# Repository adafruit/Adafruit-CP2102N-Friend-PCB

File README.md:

## Adafruit CP2102N Friend - USB to Serial Converter PCB

<a href="http://www.adafruit.com/products/5335"><br/>
Click here to purchase one from the Adafruit shop</a>

PCB files for the Adafruit CP2102N Friend - USB to Serial Converter. 

Format is EagleCAD schematic and board layout
* https://www.adafruit.com/product/5335

### Description

Long gone are the days of parallel ports and serial ports. Now the USB port reigns supreme! But USB is hard, and you just want to transfer your every-day serial data from a microcontroller to computer. What now? Enter the Adafruit CP2102N Friend!

The CP2102N is very similar to the CP2104. Despite having a name with a lower number, its actually considered the successor/next generation to the CP2104. Compared to the CP2104, the CP2102N can:

* Transfer data at a faster rate: CP2104 is 2Mbps max, the CP2102N is 3Mbps max
Reprogram the internal settings: CP2104 has a one-time-programmable memory and the CP2102N has reprogrammable settings memory. 99% of people don't use this capability but it is there if you need it.
* The CP2102N improves over the CP2012 (no N) by having the same RS-485 and GPIO support that the CP2104 has
* More details in the SiLabs CP2104 to CP2102N migration guide.
* We've also updated this breakout from our CP2104 Friend so that it has USB C instead of Micro B. It is otherwise 'drop in compatible' and anywhere you would use the CP2104 for uploading firmware to microcontrollers, it'll work exactly the same.

This is a high-quality CP2102N USB-Serial chip that can upload code at a blistering 3Mbit/s for fast development time. It also has auto-reset for Arduino/ATmega328 boards so no noodling with pins and reset button pressings. The CP2102N has better driver support than the CH340 and can do very high speeds, and variable speeds without stability issues. Compared to the FT232RL and FT231X, the CP2102N has the same capabilities or better, at a great price! It even has the RX/TX LEDs to help you debug your data, they'll blink when the chip receives/transmits data.

By default, we've set it up so that it matches our FTDI cables. The 6th pin is RTS, the power wire is +5V and the signal levels are 3.3V (they are 5V compliant, and should work in the vast majority of 3.3V and 5V signal systems). Works excellently with any Arduino, ESP8266, ESP32 or any other microcontroller that uses an 'FTDI port' for communications and upload. You can also purchase a 6-pin extension cable from us, which will let you rearrange the wire order.

There's also a full collection of all the modem control pins you may need on the side, in case you need the DTR, RI, DSR, etc. pins.

### License

Adafruit invests time and resources providing this open source design, please support Adafruit and open-source hardware by purchasing products from [Adafruit](https://www.adafruit.com)!

Designed by Limor Fried/Ladyada for Adafruit Industries.

Creative Commons Attribution/Share-Alike, all text above must be included in any redistribution. 
See license.txt for additional details.

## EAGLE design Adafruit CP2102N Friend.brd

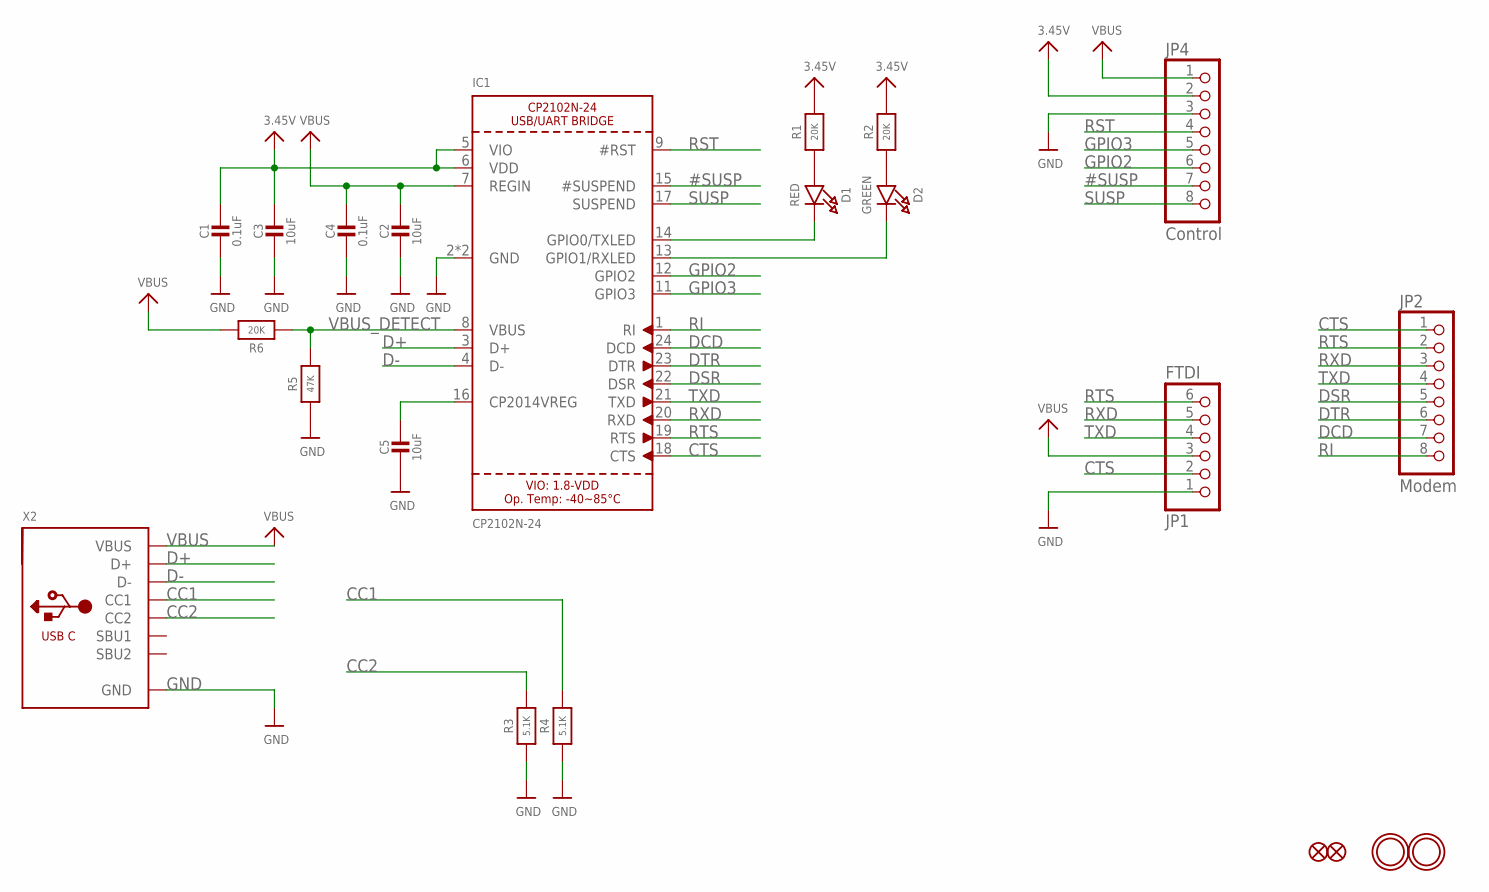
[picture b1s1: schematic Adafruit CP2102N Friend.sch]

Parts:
C1, C4: 0.1uF; 0603-NO
C2, C3, C5: 10uF; 0805-NO
D1: RED; CHIPLED_0603_NOOUTLINE
D2: GREEN; CHIPLED_0603_NOOUTLINE
FID1, FID2: FIDUCIAL_1MM
IC1: CP2102N-24; QFN24_4MM_SMSC
JP1: FTDI; 1X06_ROUND_76
JP2: Modem; 1X08_ROUND_70
JP4: Control; 1X08_ROUND_70
R1, R2, R6: 20K; 0603-NO
R3, R4: 5.1K; 0603-NO
R5: 47K; 0603-NO
U$18, U$19: MOUNTINGHOLE2.0; MOUNTINGHOLE_2.0_PLATED
X2: USB_C; USB_C_CUSB31-CFM2AX-01-X

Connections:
3.3V: C1.1, C3.1, IC1.5 (VIO), IC1.6 (VDD), JP4.2, R1.2, R2.2
#SUSP: IC1.15 (#SUSPEND), JP4.7
CC1: R4.2, X2.A5 (CC1)
CC2: R3.2, X2.B5 (CC2)
CTS: IC1.18 (CTS), JP1.2, JP2.1
D+: IC1.3 (D+), X2.A6 (D+), X2.B6 (D+)
D-: IC1.4 (D-), X2.A7 (D-), X2.B7 (D-)
DCD: IC1.24 (DCD), JP2.7
DSR: IC1.22 (DSR), JP2.5
DTR: IC1.23 (DTR), JP2.6
GND: C1.2, C2.2, C3.2, C4.2, C5.2, IC1.2 (GND), IC1.THERM (GND), JP1.1, JP4.3, R3.1, R4.1, R5.1, X2.A1B12 (GND), X2.B1A12 (GND)
GPIO2: IC1.12 (GPIO2), JP4.6
GPIO3: IC1.11 (GPIO3), JP4.5
unnamed: D1.A, R1.1
unnamed: C5.1, IC1.16 (CP2014VREG)
unnamed: D2.A, R2.1
unnamed: D1.C, IC1.14 (GPIO0/TXLED)
unnamed: D2.C, IC1.13 (GPIO1/RXLED)
RI: IC1.1 (RI), JP2.8
RST: IC1.9 (#RST), JP4.4
RTS: IC1.19 (RTS), JP1.6, JP2.2
RXD: IC1.20 (RXD), JP1.5, JP2.3
SUSP: IC1.17 (SUSPEND), JP4.8
TXD: IC1.21 (TXD), JP1.4, JP2.4
VBUS: C2.1, C4.1, IC1.7 (REGIN), JP1.3, JP4.1, R6.2, X2.A4B9 (VBUS), X2.B4A9 (VBUS)
VBUS_DETECT: IC1.8 (VBUS), R5.2, R6.1

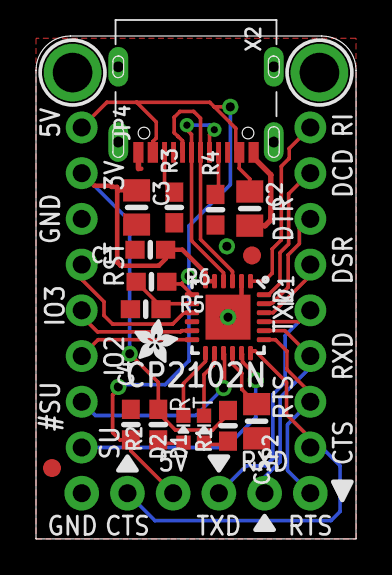
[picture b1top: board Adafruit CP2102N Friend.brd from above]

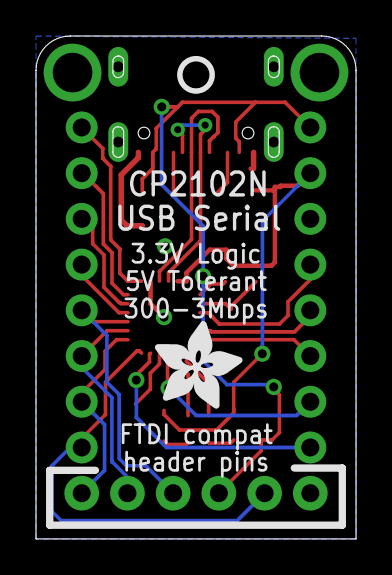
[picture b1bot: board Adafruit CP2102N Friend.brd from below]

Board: 2 copper layers, 17.8 x 27.9 mm, 25 parts (2 on the bottom side), 26 nets.

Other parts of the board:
U$8: ADAFRUIT_2.5MM
U$17: PCBFEAT-REV-040
U$22: ADAFRUIT_5MM

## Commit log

2022-02-21 add fab and schem PNGs

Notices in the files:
parts and their libraries:
microbuilder: This work is placed in the public domain, and may be freely used for commercial and non-commercial work with the following conditions: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
